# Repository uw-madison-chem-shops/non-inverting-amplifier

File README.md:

# non-inverting-amplifier

A very simple non-inverting amplifier.

## PCB

This PCB was designed using KiCAD version 7.
Refer to `DC_Amplifier.pdf` for schematic.
PCB images generated with [tracespace](https://github.com/tracespace/tracespace) follow.

Bill of Materials

| reference      | value          | manufacturer | part number          | vendors |
| :------------- | :------------- | :----------- | :------------------- | :------ |
| C1, C2         | 100 uF         | TDK          | C3216X5R1A107M160AC  | [DigiKey](https://www.digikey.com/en/products/detail/tdk-corporation/C3216X5R1A107M160AC/2444048) [Newark](https://www.newark.com/tdk/c3216x5r1a107m160ac/ceramic-capacitor-100uf-10v-x5r/dp/04X3294?st=c3216x5r1a107m160ac) |
| J1             | power entry    | Molex        | 22-23-2031           | [DigiKey](https://www.digikey.com/en/products/detail/molex/0022232031/26669?s=N4IgTCBcDa5gtGAzIgDEgjCAugXyA) [Newark](https://www.newark.com/molex/22-23-2031/connector-header-3pos-1row-2-54mm/dp/30C0862?ost=0022232031) |
| J2, J3         | source, output | Molex        | 0732512120           | [DigiKey](https://www.digikey.com/en/products/detail/molex/0732512120/1465158?s=N4IgTCBcDaIAQAYDsBmMBWAjGbCQF0BfIA) |
| R1             | 1k             | Yageo        | RC1206FR-071KL       | [DigiKey](https://www.digikey.com/en/products/detail/yageo/RC1206FR-071KL/728387?s=N4IgTCBcDaIAQCUDCBGMAGAbAMQQWnQHYUBpAGRAF0BfIA) [Newark](https://www.newark.com/yageo-phycomp/rc1206fr-071kl/thick-film-resistor-1kohm-250mw/dp/98K7619?st=rc1206fr-071kl) |
| RV1            | 100k trimpot   | Bourns       | 3296W-1-104LF        | [DigiKey](https://www.digikey.com/en/products/detail/bourns-inc/3296W-1-104LF/1088046?s=N4IgjCBcoLQBxVAYygMwIYBsDOBTANCAPZQDa4YCAugL42EBMZIAzAwJwBsA6jGHwAYALABkAYiFpA) [Newark](https://www.newark.com/bourns/3296w-1-104lf/trimmer-potentiometer-100kohm/dp/62J1426?st=3296w-1-104lf) |
| TP1, TP2       | yellow         | Keystone     | 5014                 | [DigiKey](https://www.digikey.com/en/products/detail/keystone-electronics/5014/255336) |
| TP3            | green          | Keystone     | 5126                 | [DigiKey](https://www.digikey.com/en/products/detail/keystone-electronics/5126/2170329) |
| TP4            | black          | Keystone     | 5011                 | [DigiKey](https://www.digikey.com/en/products/detail/keystone-electronics/5011/255333) |
| TP5            | red            | Keystone     | 5010                 | [DigiKey](https://www.digikey.com/en/products/detail/keystone-electronics/5010/255332) |
| U1             | OP-AMP         | Analog       | OP27GPZ              | [DigiKey](https://www.digikey.com/en/products/detail/analog-devices-inc/OP27GPZ/820340?s=N4IgTCBcDaIPYAcwHYDmCBeIC6BfIA) [Newark](https://www.newark.com/analog-devices/op27gpz/operational-amplifier-single-8/dp/34X1906?ost=op27gpz) |

## Changelog

### B

#### Changed
- prepared for professional printing
- changed to surface-mount passives

### A

#### Added
- initial design

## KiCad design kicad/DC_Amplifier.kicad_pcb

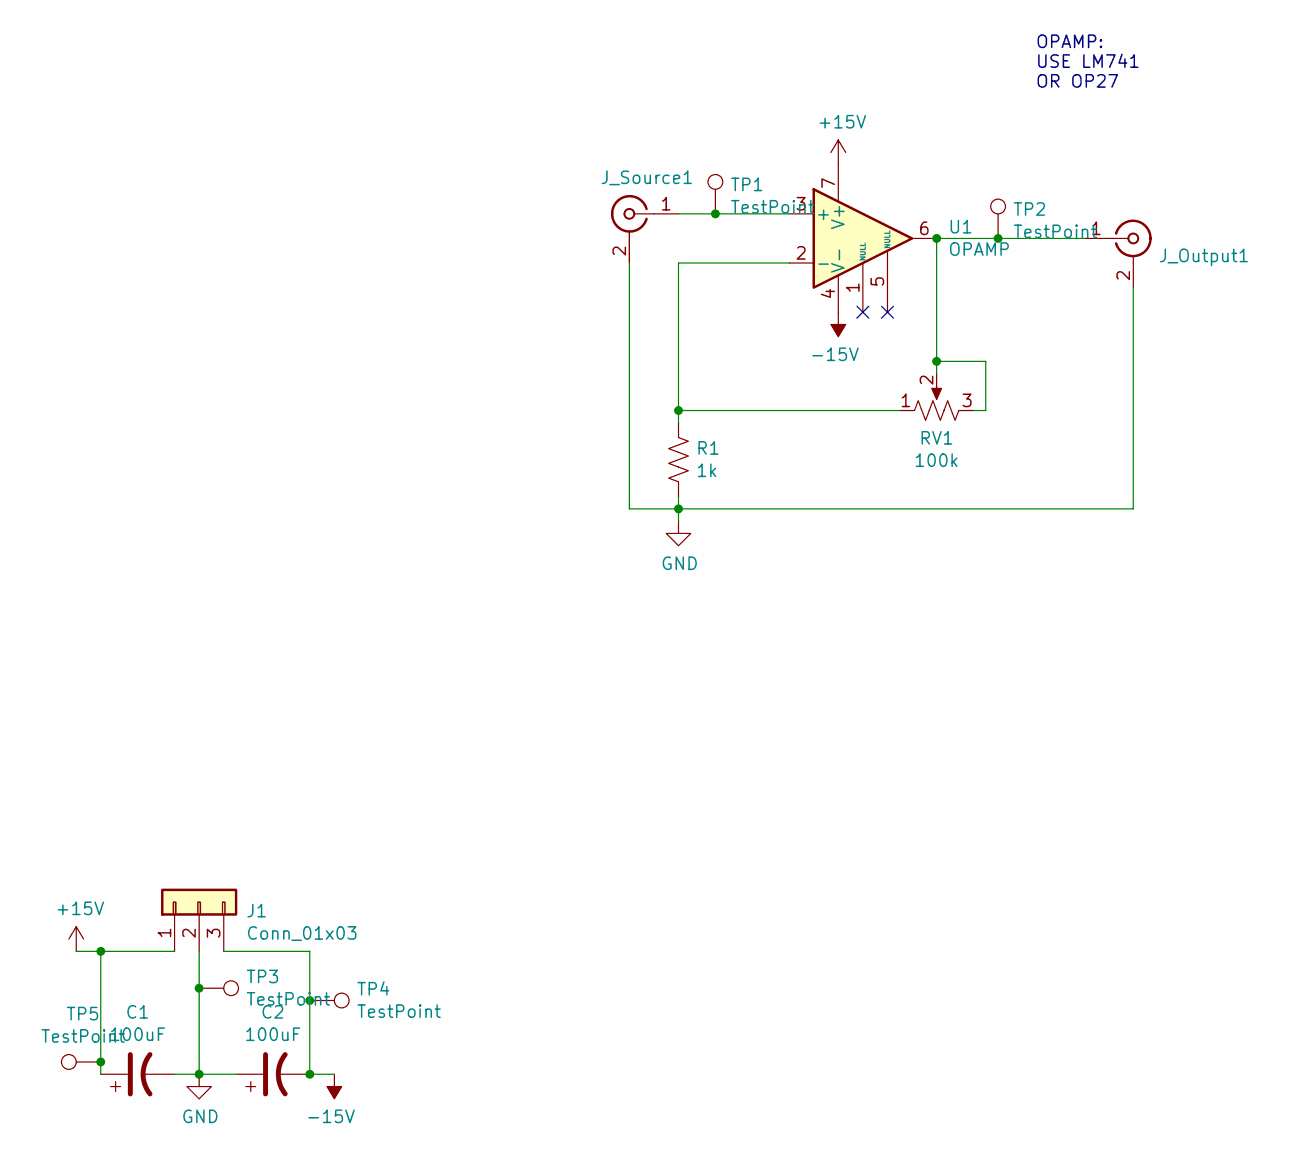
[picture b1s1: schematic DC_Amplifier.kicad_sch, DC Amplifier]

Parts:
C1, C2: 100uF; C_1206_3216Metric_Pad1.33x1.80mm_HandSolder
J1: Conn_01x03; Molex_KK-254_AE-6410-03A_1x03_P2.54mm_Vertical
J_Output1: Conn_Coaxial; 0732512120
J_Source1: Conn_Coaxial; 0732512120
R1: 1k; R_1206_3216Metric_Pad1.30x1.75mm_HandSolder
RV1: 100k; Potentiometer_Bourns_3296W_Vertical
TP1, TP2, TP3, TP4, TP5: TestPoint; TestPoint_THTPad_D3.0mm_Drill1.5mm
U1: OPAMP; DIP-8_W7.62mm_LongPads

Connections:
+15V: C1.1, J1.1, TP5.1, U1.7 (V+)
-15V: C2.2, J1.3, TP4.1, U1.4 (V-)
GND: C1.2, C2.1, J1.2, J_Output1.2 (Ext), J_Source1.2 (Ext), R1.2, TP3.1
unnamed: J_Output1.1 (In), RV1.2, RV1.3, TP2.1, U1.6
unnamed: J_Source1.1 (In), TP1.1, U1.3 (+)
unnamed: R1.1, RV1.1, U1.2 (-)

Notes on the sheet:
OPAMP: USE LM741 OR OP27

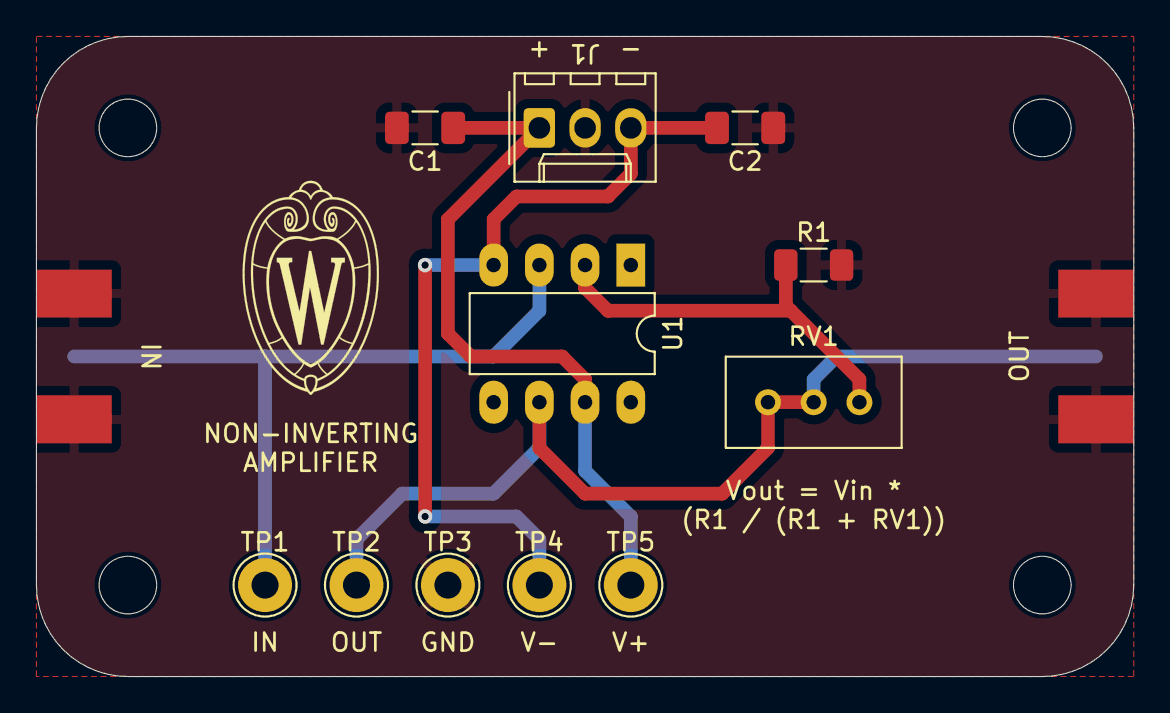
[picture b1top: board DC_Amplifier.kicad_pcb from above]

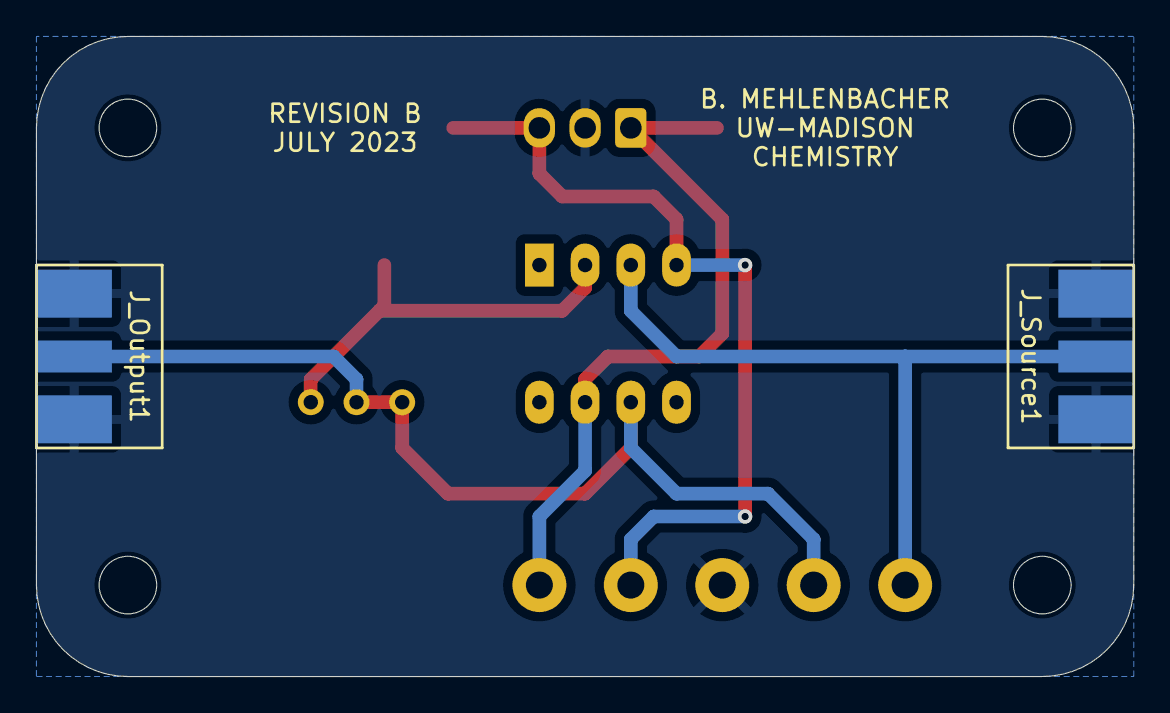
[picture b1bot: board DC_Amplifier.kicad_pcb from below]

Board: 2 copper layers, 61.0 x 35.6 mm, 13 parts (2 on the bottom side), 6 nets.

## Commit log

2023-07-10 rearrange directories
2023-07-18 kicad 7
